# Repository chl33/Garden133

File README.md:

# Garden133 (v1.1.0)

Garden133 is a solar and battery-powered device for monitoring garden soil moisture levels.
It reads the moisture level of soil using a capacitive moisture sensor and transmits data via LoRa.

Please see the [Introducing Garden133](https://selectiveappeal.org/posts/garden133/) blog
post for a project overview.

## Features
- **Modern Web Interface:** A responsive Svelte-based UI for real-time status monitoring and calibration (accessible in Debug Mode).
- **Soil Moisture Sensing:** Capacitive sensor measurement with high-precision calibration and low-voltage filtering protection.
- **Dedicated Calibration Page:** View live ADC counts to precisely tune dry/wet thresholds.
- **Device Environmental Monitoring:** SHTC3 sensor for air temperature and humidity inside the device enclosure.
- **Power Management:** Solar charging, battery/5V rail monitoring, TP4056 charge/standby status reporting (Board v6+), and P-MOSFET moisture sensor power gating during deep sleep (Board v7+).
- **LoRa Communication:** Supports both HopeRF RFM95W (`SX1276`, Board v5–v7) and Ai-Thinker Ra-01SH (`SX1262`, Board v8+) modules to connect to a base station ([LoRa133](https://github.com/chl33/LoRa133)) for Home Assistant integration.
- **OTA Updates:** Support for wireless firmware updates.

## Hardware
This project includes the custom hardware design and 3D printable parts.

- **PCB Design:** KiCAD files are available in [`KiCAD/Garden133/`](KiCAD/Garden133/).
  - **Board v6.x:** Adds TP4056 charge/standby status inputs.
  - **Board v7.0:** Adds P-channel MOSFET (`AO3401A` on GPIO25) to power off the capacitive moisture sensor during sleep.
  - **Board v8.0:** Transitions to the Ai-Thinker Ra-01SH (`SX1262`) LoRa transceiver and an active-low debug DIP switch with external pull-up.
  
- **Enclosure & Fixtures:** OpenSCAD files for the waterproof enclosure, desiccant inserts, mounts, and solder-paste stencil fixtures are in [`OpenSCAD/`](OpenSCAD/).

## Firmware Dependencies
This firmware uses the [PlatformIO](https://platformio.org/) build system and depends on the following libraries:
- [og3](https://github.com/chl33/og3): Base C++ library for ESP32/Arduino.
- [og3x-lora](https://github.com/chl33/og3x-lora): LoRa module support (`SX1276` and `SX1262` via RadioLib).
- [og3x-satellite](https://github.com/chl33/og3x-satellite): Satellite architecture support.
- [og3x-shtc3](https://github.com/chl33/og3x-shtc3): SHTC3 temperature and humidity sensor support.

## Getting Started

### Prerequisites
- [PlatformIO Core](https://docs.platformio.org/en/latest/core/index.html) or VSCode with PlatformIO extension.
- Node.js (v22+) and `npm` (for building the embedded Svelte web UI).
- An ESP32-based Garden133 board.

### Configuration
The project uses `secrets.ini` and `local.ini` for local configuration and board definitions (both excluded from git):

1. **Setup Secrets & Local Board Environments:**
   Copy the example configuration files:
   ```bash
   cp secrets.ini.example secrets.ini
   cp local.ini.example local.ini
   ```
   - Edit `secrets.ini` to set `otaPassword` for Over-The-Air updates.
   - Edit `local.ini` to configure your board's `HARDWARE_VERSION_MAJOR` / `HARDWARE_VERSION_MINOR` (e.g., `6.2`, `7.0`, or `8.0`), upload port/IP, and optional UDP debug logging.

### Building & Flashing

1. **Build the firmware:**
   ```bash
   pio run
   ```

2. **Upload the firmware:**
   ```bash
   pio run --target upload
   ```

3. **Upload Filesystem (LittleFS):**
   This uploads the `data/` directory containing web resources.
   ```bash
   pio run --target uploadfs
   ```

## License
This project is licensed under the MIT License. See `LICENSE` for details.

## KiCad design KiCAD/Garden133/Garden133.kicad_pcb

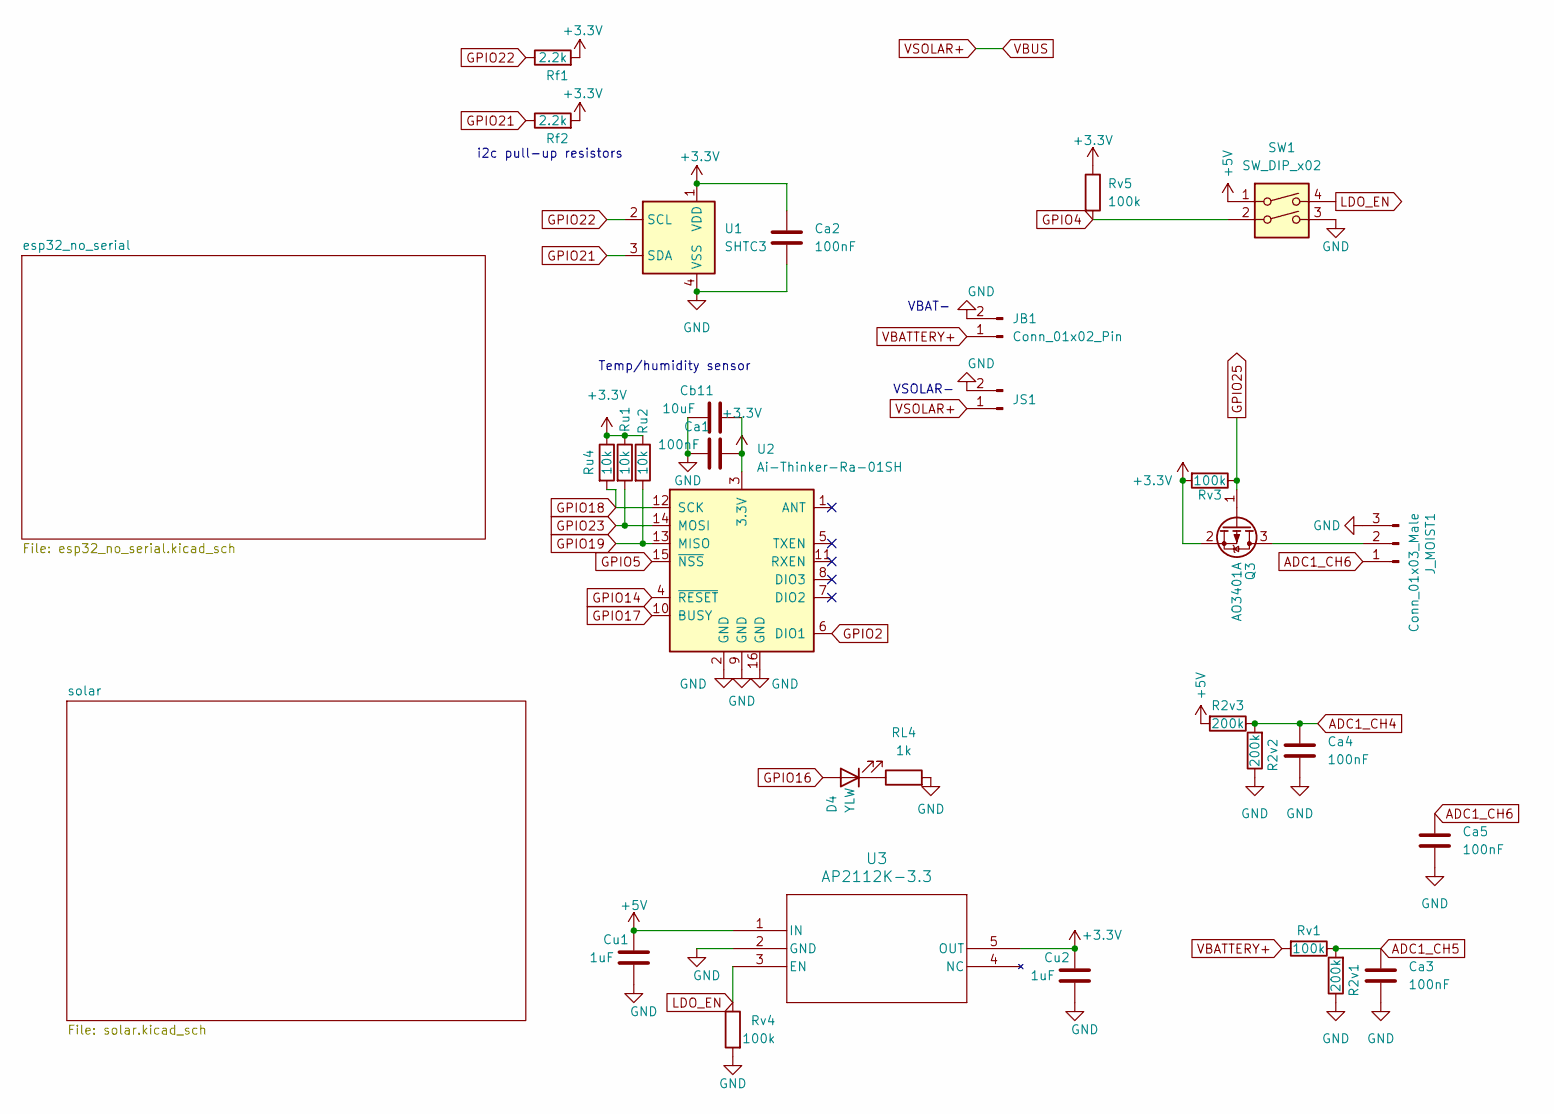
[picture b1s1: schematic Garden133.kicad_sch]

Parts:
Ca1, Ca2: 100nF; C_0603_1608Metric
Ca3, Ca4, Ca5: 100nF; C_0603_1608Metric_Pad1.08x0.95mm_HandSolder
Cb11: 10uF; C_0805_2012Metric_Pad1.18x1.45mm_HandSolder
Cu1, Cu2: 1uF; C_0805_2012Metric_Pad1.18x1.45mm_HandSolder
D4: YLW; LED_0603_1608Metric_Pad1.05x0.95mm_HandSolder
JB1: Conn_01x02_Pin; MOLEX_530470210
JS1: Conn_01x02_Pin; JST_XH_B2B-XH-A_1x02_P2.50mm_Vertical
J_MOIST1: Conn_01x03_Male; JST_XH_B3B-XH-A_1x03_P2.50mm_Vertical
Q3: AO3401A; SOT-23
R2v1, R2v2, R2v3: 200k; R_0603_1608Metric
RL4: 1k; R_0603_1608Metric_Pad0.98x0.95mm_HandSolder
Rf1, Rf2: 2.2k; R_0603_1608Metric
Ru1, Ru2, Ru4: 10k; R_0603_1608Metric
Rv1, Rv3, Rv4, Rv5: 100k; R_0603_1608Metric
SW1: SW_DIP_x02; SW_DIP_SPSTx02_Slide_6.7x6.64mm_W6.73mm_P2.54mm_LowProfile_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
U1: SHTC3; Sensirion_DFN-4-1EP_2x2mm_P1mm_EP0.7x1.6mm
U2: Ai-Thinker-Ra-01SH; Ai-Thinker-Ra-01-LoRa
U3: AP2112K-3.3; SOT-23-5

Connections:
+3.3V: Ca1.2, Ca2.1, Cb11.2, Cu2.1, Q3.2 (S), Rf1.2, Rf2.2, Ru1.1, Ru2.1, Ru4.1, Rv3.2, Rv5.1, U1.1 (VDD), U2.3 (3.3V), U3.5 (OUT); also elsewhere on the board
+5V: Cu1.1, R2v3.2, SW1.1, U3.1 (IN); also elsewhere on the board
ADC1_CH4: Ca4.2, R2v2.2, R2v3.1; also elsewhere on the board
ADC1_CH5: Ca3.2, R2v1.2, Rv1.1; also elsewhere on the board
ADC1_CH6: Ca5.2, J_MOIST1.1; also elsewhere on the board
GND: Ca1.1, Ca2.2, Ca3.1, Ca4.1, Ca5.1, Cb11.1, Cu1.2, Cu2.2, JB1.2, JS1.2, J_MOIST1.3, R2v1.1, R2v2.1, RL4.2, Rv4.2, SW1.3, U1.4 (VSS), U2.2 (GND), U2.9 (GND), U2.16 (GND), U3.2 (GND); also elsewhere on the board
GPIO2: U2.6 (DIO1); also elsewhere on the board
GPIO4: Rv5.2, SW1.2; also elsewhere on the board
GPIO5: U2.15 (~NSS); also elsewhere on the board
GPIO14: U2.4 (~RESET); also elsewhere on the board
GPIO16: D4.2 (A); also elsewhere on the board
GPIO17: U2.10 (BUSY); also elsewhere on the board
GPIO18: Ru4.2, U2.12 (SCK); also elsewhere on the board
GPIO19: Ru2.2, U2.13 (MISO); also elsewhere on the board
GPIO21: Rf2.1, U1.3 (SDA); also elsewhere on the board
GPIO22: Rf1.1, U1.2 (SCL); also elsewhere on the board
GPIO23: Ru1.2, U2.14 (MOSI); also elsewhere on the board
GPIO25: Q3.1 (G), Rv3.1; also elsewhere on the board
LDO_EN: Rv4.1, SW1.4, U3.3 (EN)
unnamed: D4.1 (K), RL4.1
unnamed: J_MOIST1.2, Q3.3 (D)
VBATTERY+: JB1.1, Rv1.2; also elsewhere on the board
VBUS: JS1.1; also elsewhere on the board

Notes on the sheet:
VSOLAR-
Temp/humidity sensor
i2c pull-up resistors
VBAT-

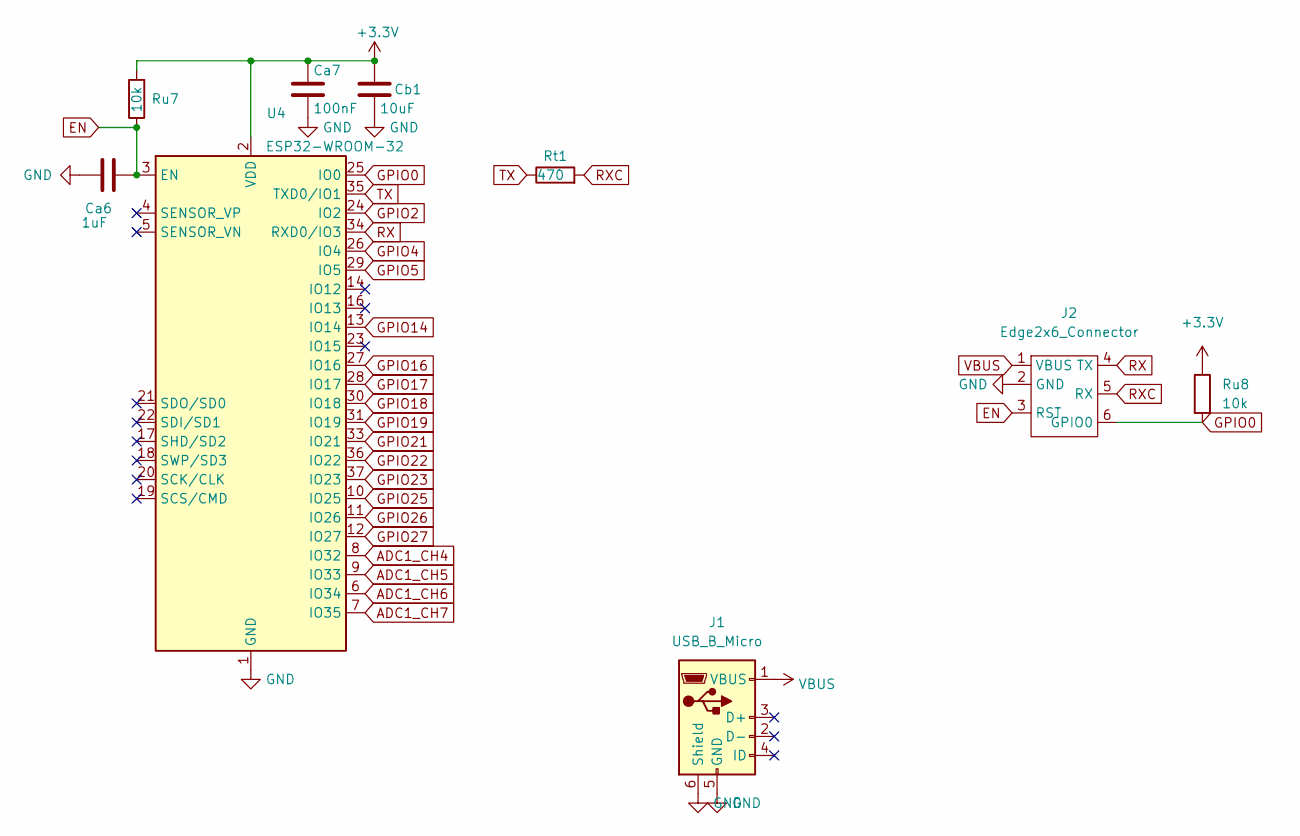
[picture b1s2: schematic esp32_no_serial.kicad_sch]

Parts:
Ca6: 1uF; C_0603_1608Metric
Ca7: 100nF; C_0603_1608Metric
Cb1: 10uF; C_0805_2012Metric_Pad1.18x1.45mm_HandSolder
J1: USB_B_Micro; USB_Micro-B_Amphenol_10118194_Horizontal
J2: Edge2x6_Connector; EdgeConnector_2x3
Rt1: 470; R_0603_1608Metric
Ru7: 10k; R_0603_1608Metric
Ru8: 10k; R_0603_1608Metric_Pad0.98x0.95mm_HandSolder
U4: ESP32-WROOM-32

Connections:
+3.3V: Ca7.1, Cb1.1, Ru7.2, Ru8.1, U4.2 (VDD); also elsewhere on the board
ADC1_CH4: U4.8 (IO32); also elsewhere on the board
ADC1_CH5: U4.9 (IO33); also elsewhere on the board
ADC1_CH6: U4.6 (IO34); also elsewhere on the board
ADC1_CH7: U4.7 (IO35); also elsewhere on the board
EN: Ca6.2, J2.3 (RST), Ru7.1, U4.3 (EN)
GND: Ca6.1, Ca7.2, Cb1.2, J1.5 (GND), J1.6 (Shield), J2.2 (GND), U4.1 (GND), U4.15 (GND), U4.38 (GND), U4.39 (GND); also elsewhere on the board
GPIO0: J2.6 (GPIO0), Ru8.2, U4.25 (IO0)
GPIO2: U4.24 (IO2); also elsewhere on the board
GPIO4: U4.26 (IO4); also elsewhere on the board
GPIO5: U4.29 (IO5); also elsewhere on the board
GPIO14: U4.13 (IO14); also elsewhere on the board
GPIO16: U4.27 (IO16); also elsewhere on the board
GPIO17: U4.28 (IO17); also elsewhere on the board
GPIO18: U4.30 (IO18); also elsewhere on the board
GPIO19: U4.31 (IO19); also elsewhere on the board
GPIO21: U4.33 (IO21); also elsewhere on the board
GPIO22: U4.36 (IO22); also elsewhere on the board
GPIO23: U4.37 (IO23); also elsewhere on the board
GPIO25: U4.10 (IO25); also elsewhere on the board
GPIO26: U4.11 (IO26); also elsewhere on the board
GPIO27: U4.12 (IO27); also elsewhere on the board
RX: J2.4 (TX), U4.34 (RXD0/IO3)
RXC: J2.5 (RX), Rt1.2
TX: Rt1.1, U4.35 (TXD0/IO1)
VBUS: J1.1 (VBUS), J2.1 (VBUS); also elsewhere on the board

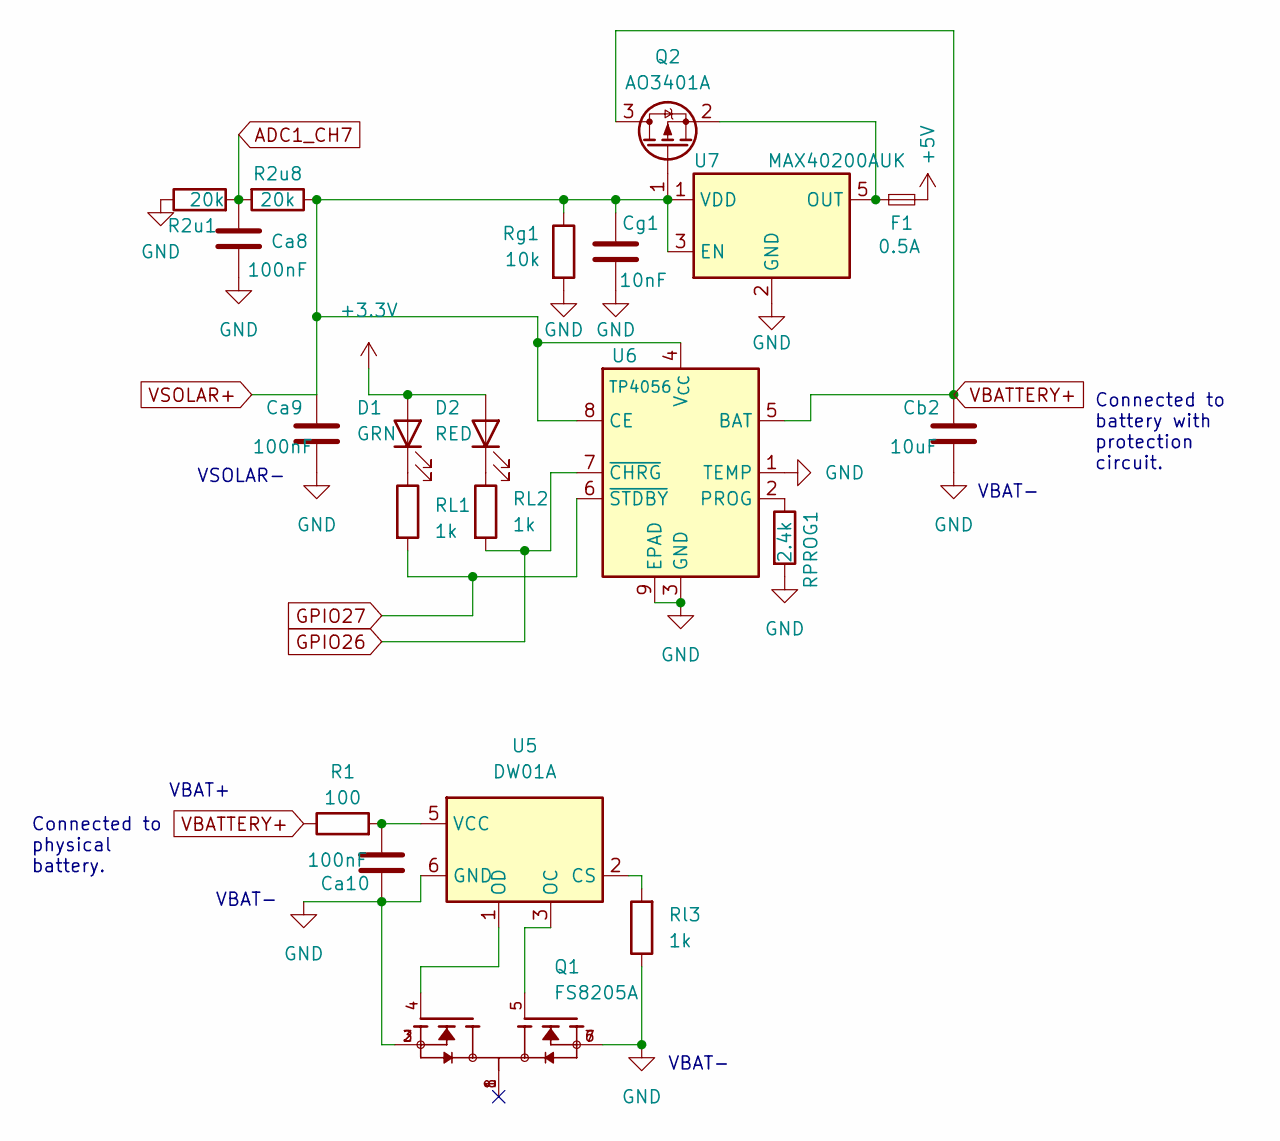
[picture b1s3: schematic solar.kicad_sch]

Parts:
Ca8, Ca9, Ca10: 100nF; C_0603_1608Metric_Pad1.08x0.95mm_HandSolder
Cb2: 10uF; C_0805_2012Metric_Pad1.18x1.45mm_HandSolder
Cg1: 10nF; C_0603_1608Metric_Pad1.08x0.95mm_HandSolder
D1: GRN; LED_0603_1608Metric_Pad1.05x0.95mm_HandSolder
D2: RED; LED_0603_1608Metric_Pad1.05x0.95mm_HandSolder
F1: 0.5A; D_0805_2012Metric
Q1: FS8205A; SOP65P640X120-8N; PARTREV 1.7
Q2: AO3401A; SOT-23
R1: 100; R_0603_1608Metric_Pad0.98x0.95mm_HandSolder
R2u1: 20k; R_0603_1608Metric_Pad0.98x0.95mm_HandSolder
R2u8: 20k; R_0603_1608Metric
RL1, RL2: 1k; R_0603_1608Metric_Pad0.98x0.95mm_HandSolder
RPROG1: 2.4k; R_0603_1608Metric_Pad0.98x0.95mm_HandSolder
Rg1: 10k; R_0603_1608Metric_Pad0.98x0.95mm_HandSolder
Rl3: 1k; R_0603_1608Metric_Pad0.98x0.95mm_HandSolder
U5: DW01A; SOT-23-6; LCSC C61503
U6: TP4056; SOIC-8-1EP_3.9x4.9mm_P1.27mm_EP2.41x3.3mm_ThermalVias
U7: MAX40200AUK; SOT-23-5

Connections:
+3.3V: D1.2 (A), D2.2 (A); also elsewhere on the board
+5V: F1.2; also elsewhere on the board
ADC1_CH7: Ca8.2, R2u1.2, R2u8.2; also elsewhere on the board
GND: Ca8.1, Ca9.2, Ca10.2, Cb2.2, Cg1.2, Q1.2, Q1.3, Q1.6, Q1.7, R2u1.1, RPROG1.2, Rg1.2, Rl3.1, U5.6 (GND), U6.1 (TEMP), U6.3 (GND), U6.9 (EPAD), U7.2 (GND); also elsewhere on the board
GPIO26: RL2.2, U6.7 (~CHRG); also elsewhere on the board
GPIO27: RL1.2, U6.6 (~STDBY); also elsewhere on the board
unnamed: D1.1 (K), RL1.1
unnamed: D2.1 (K), RL2.1
unnamed: F1.1, Q2.2 (S), U7.5 (OUT)
unnamed: Rl3.2, U5.2 (CS)
unnamed: Q1.5, U5.3 (OC)
unnamed: Q1.4, U5.1 (OD)
unnamed: Ca10.1, R1.2, U5.5 (VCC)
unnamed: RPROG1.1, U6.2 (PROG)
VBATTERY+: Cb2.1, Q2.3 (D), R1.1, U6.5 (BAT); also elsewhere on the board
VBUS: Ca9.1, Cg1.1, Q2.1 (G), R2u8.1, Rg1.1, U6.4 (V_{CC}), U6.8 (CE), U7.1 (VDD), U7.3 (EN); also elsewhere on the board

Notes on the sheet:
VBAT-
Connected to battery with protection circuit.
VBAT+
Connected to physical battery.
VSOLAR-

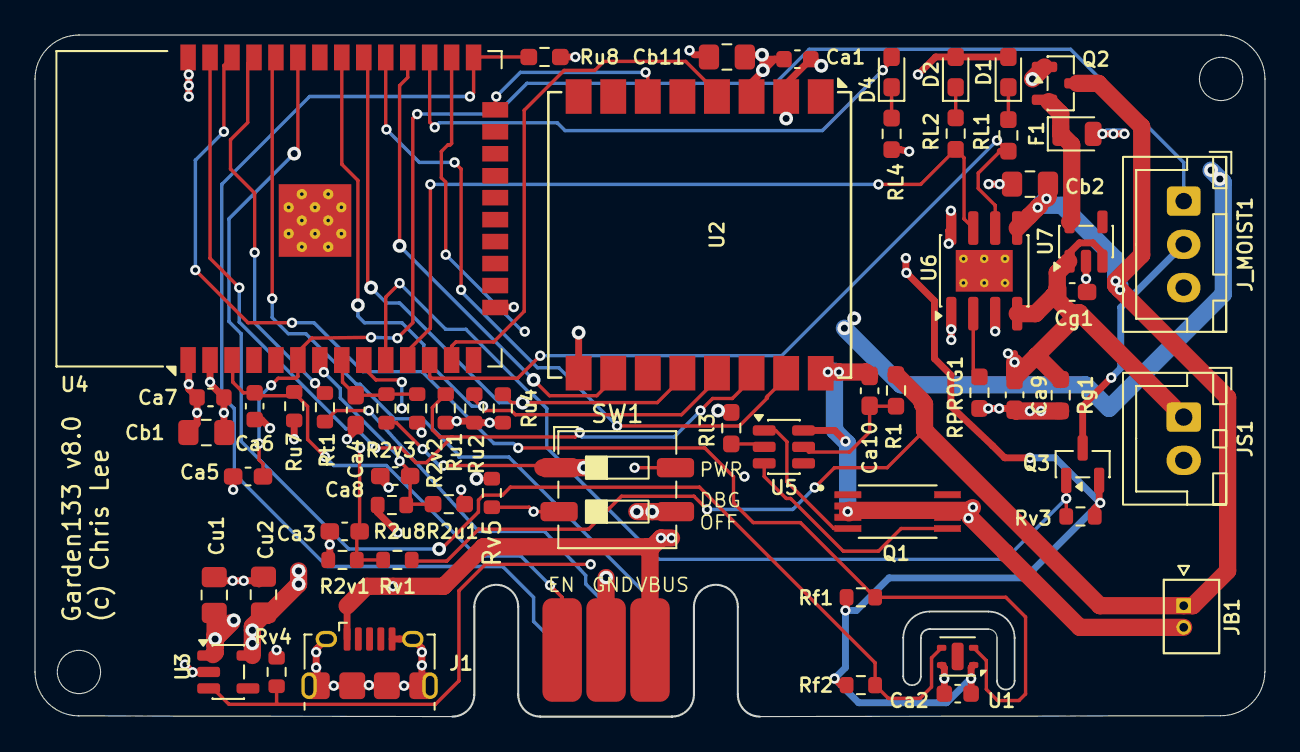
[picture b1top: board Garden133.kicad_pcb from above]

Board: 4 copper layers, 71.0 x 39.4 mm, 60 parts (0 on the bottom side), 39 nets.

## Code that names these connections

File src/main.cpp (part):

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constexpr int kLoraDio0 = 2;
#endif

constexpr int kFiveVPin = 32;      // ADC1_CH4
constexpr int kBatteryPin = 33;    // ADC1_CH5
constexpr int kMoisturePin = 34;   // ADC1_CH6
constexpr int kSolarPlusPin = 35;  // ADC1_CH7
#ifdef HAVE_MOISTURE_POWER_CTL
// Gate control for AO3401A P-FET moisture sensor power switch
constexpr int kMoisturePowerPin = 25;
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constexpr int kDebugSwitchPin = 04;
inline bool read_debug_switch() {
#if HARDWARE_VERSION_MAJOR >= 8
  // Board v8+: Switch 2 connects GPIO4 to GND with external pull-up Rv5.
  // Switch ON (closed) = GND (LOW) -> Debug Mode.
  return digitalRead(kDebugSwitchPin) == LOW;
#else
  // Board < v8: Push switch connects GPIO4 to 3.3V when activated.
  // HIGH -> Debug Mode.
  return digitalRead(kDebugSwitchPin) == HIGH;
#endif
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
  while (true) {
    // --- Test 1: BUSY pin pull-up / pull-down float check ---
    Serial.println("\n--- [Test 1] BUSY Pin (Pin 10 / GPIO17) Connection Check ---");
    pinMode(17, INPUT_PULLUP);
    delay(2);
    int busy_pu = digitalRead(17);
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
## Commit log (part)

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2025-06-15 initial version
2025-06-15 code moved to og3
2025-06-15 Update for board v6
    - Added OpenSCAD models for Solar panel mount, tray for board+battery
    - ADC Adjustment because using 220k resistors, not 200k.
    - Licenses updated
    - Remove support for v4 boards, update ADC slopes
    - Board v6.0 (ordered)
    - Support publishing more data via LoRa.
2025-06-15 Soil-sensor potting case update
2025-06-15 Read temp/humidity and moisture sensors, and send via LoRa+MQTT
2025-06-15 solar ADC divide-down is now 2
2025-06-15 ADC counts change from number -> unspecified
2025-06-15 Soil moisture sensor potting frame -- initial version
2025-06-15 WIP -- KiCAD, packet format, device protos
2025-06-15 Send full device info every hour, brief info otherwise.
2025-06-15 Update PCB
    - Button controls power to 3.3V LDO
    - DIO readings for STDBY and CHRG
2025-06-15 Board version 5
2025-06-15 Updated device protobuf, got LoRa working.
2025-06-15 Allow turning-off debug mode.
    Note that this does not power-down WiFi.
2025-06-15 support blinking the LED
2025-06-15 Soil moisture sensor potting frame -- version 2
2025-06-15 First draft of new moisture sensor cap
2025-06-15 og3->0.3.16, use crc32 for LoRa packets, ignore moisture when <3.3V
2025-06-15 Solar panel holder for smaller panel
2025-06-15 Register moisture reading as "measurement" state-class for HA stats
2025-06-15 Attempt to avoid brown-out during desc-send
    Adjustments to deal with the fact that boards seemed to be browning-out when
    descriptions packets were being sent every second. Maybe the LDO+capacitors
    cannot keep up with this level of power usage?
    - Slow desc-sends to 1 every 5 seconds.
    - Make sure serial logging is turned off after USB code update.
    Maybe the board needs a bulk capacitor for 3.3V?
2025-06-15 Update: version -> 0.4.0
    - Fix boot-count, seq_id
    - Had initializers for some rtc values such as boot count, so these were being
    reset after sleep.
    - Fix logic for sending sensor-reading descriptions every hour.
    - Board stays alive a short time after sending messages to blink led.
2025-06-15 Better use of constants
2025-06-15 Garden133 Board v6.2 (ordered from PCBWay)
2025-06-15 Fix sleep timing
2025-06-15 version tweaks
2025-06-15 Use updates to og3x-lora, new og3x-satellite repositories.
    - Allow LoRa to be configurable via web interface.
    - Check payload size for US FCC reg (400msec max dwell).
2025-06-15 Fix led-blinking
2025-06-15 boards update
2025-06-15 Version 4a of moisture sensor cap
    - Shorter
    - Thinner slot for sensor board.
    - Shrink hole for connector
2025-06-15 cleanup platform.ini
2025-06-15 Update how config determines text-logging method
2025-06-15 Version 2 of moisture sensor cap
    - More space for connector
    - Tighter hole for sensor
    - Clamp top & bottom around the wire.
2025-06-15 Version 4 of moisture sensor cap
    - Shorter
    - Thinner slot for sensor board.
    - Shrink hole for connector
2025-06-15 Cleanup loop()
2025-06-15 Fixes to avoid brown-outs
    - Only send one packet between sleeping after initial sensor descriptions are sent.
    - Each hour, for the first N-packets, send information about the N-th sensor.
    In the first packet send the device info.
    - The board reliably browns-out after sending 2 LoRa packets and never recovers, when
    battery-powered at least (and maybe also when connected to the moisture sensor).
    - Add more bits to the boot-count in rtc memory. It was going to roll over after 45
2025-06-15 Attempt to make sleep configurable, more consistent wakeup.
2025-06-15 OpenSCAD: waterproof enclosure, stls for soil moisture cap
2025-06-15 Version 3 of moisture sensor cap
    - Thicker minimum wall thickness.
    - More space at top of connector for wire into JST
    - Lip at side of box to lock it into place
    - Screw holes near top (away from point) of sensor)
2025-06-15 fix link
2025-06-19 Fix 20k resistor (was 10k)
2025-06-19 Board v6.2 update: standby/charge detection.
    Maybe also fix hourly update?
2025-06-19 Example secrets pio config
2025-06-19 update for board v6.2 (#1)
    - Fix 20k resistor
    - Board v6.2 update: standby/charge detection
    -Maybe also fix hourly update?
2025-06-22 KiCAD model: remove duplicate battery connection
2025-06-22 Fix for standby/charge DIn detection
2025-06-22 Updates (#2)
    * KiCAD model: remove duplicate battery connection
    * Fix for standby/charge DIn detection
2025-07-07 KiCAD v62 fixes, README update, code update (#3)
    * KiCAD model: remove duplicate battery connection
    * Code: Fix for standby/charge DIn detection
    * Update README
2025-07-19 version -> 0.6.0
    - Used updated og3x-satellite with updated protocol
    - Set board name as device name in device protobuf
    - Set model name as device_type (new field) in device protobuf
2025-07-19 version -> 0.6.0 (#4)
    - Used updated og3x-satellite with updated protocol
    - Set board name as device name in device protobuf
    - Set model name as device_type (new field) in device protobuf
2025-10-18 Update moisture cap -- needs testing
2025-10-18 shorten cap, add more space for connector
2025-10-18 Slightly more space for soil moisture sensor in y direction
2025-10-18 shorten screw-hole
2025-10-19 moisture cap STL file update
2025-10-19 dependency cleanups, code comments
2025-10-19 soil moisture cap update (#5)
    - Updated soil moisture cap design.
    - Depdencency cleanups to get the build to work again.
    - Code-comment edits
2026-01-28 board updates
2026-01-28 README updates
2026-01-28 platform.ini: update dependencies
2026-01-28 added uploadHostPort to secrets example
2026-01-28 Board update, README update (#6)
    - Board updae
    - README update, assisted by Gemini.
    - Bump dependencies.
2026-03-22 license-check update
2026-03-22 update to newer og3x-lora (gemini)
2026-03-22 Gemini updates to get the code to compile
2026-03-22 let /lora URL handle POSTs
2026-03-25 gemini fixes for new dependency system
2026-03-29 copyright headers
2026-03-29 Svelte interface (gemini)
2026-03-31 start of local board reconfiguration
2026-03-31 web interface fixes (gemini)
2026-03-31 Separate moisture sensor calibration page (gemini)
2026-04-01 reordered adc reading
2026-04-01 opened board in kicad
2026-04-02 platformio.ini: update deps to public versions
2026-04-02 Updates for version 1.0.0
2026-04-03 Add local.ini.example, use in github action CI build
2026-04-03 Add web interface to README
2026-04-03 update build workflow for Svelta build
2026-04-03 Version 1.0.0 (#7)
    ## [1.0.0] - 2026-03-29
    ### Added
    - New responsive Svelte web interface for status monitoring and configuration (Debug Mode).
    - JSON API for full device control and status reporting.
    - Standardized `camelCase` naming for all API keys and internal variables.
    - Dedicated Moisture Calibration page with live ADC count monitoring.
2026-04-03 Bump actions/setup-python from 5 to 6
    Bumps [actions/setup-python](https://github.com/actions/setup-python) from 5 to 6.
    - [Release notes](https://github.com/actions/setup-python/releases)
    - [Commits](https://github.com/actions/setup-python/compare/v5...v6)
    ---
    updated-dependencies:
    - dependency-name: actions/setup-python
2026-04-03 Bump actions/setup-node from 4 to 6
    Bumps [actions/setup-node](https://github.com/actions/setup-node) from 4 to 6.
    - [Release notes](https://github.com/actions/setup-node/releases)
    - [Commits](https://github.com/actions/setup-node/compare/v4...v6)
    ---
    updated-dependencies:
    - dependency-name: actions/setup-node
2026-04-03 Bump actions/cache from 4 to 5
    Bumps [actions/cache](https://github.com/actions/cache) from 4 to 5.
    - [Release notes](https://github.com/actions/cache/releases)
    - [Changelog](https://github.com/actions/cache/blob/main/RELEASES.md)
    - [Commits](https://github.com/actions/cache/compare/v4...v5)
    ---
    updated-dependencies:
2026-04-03 Bump actions/checkout from 4 to 6
    Bumps [actions/checkout](https://github.com/actions/checkout) from 4 to 6.
    - [Release notes](https://github.com/actions/checkout/releases)
    - [Changelog](https://github.com/actions/checkout/blob/main/CHANGELOG.md)
    - [Commits](https://github.com/actions/checkout/compare/v4...v6)
    ---
    updated-dependencies:
2026-06-18 Bump actions/checkout from 4 to 7
    Bumps [actions/checkout](https://github.com/actions/checkout) from 4 to 7.
    - [Release notes](https://github.com/actions/checkout/releases)
    - [Changelog](https://github.com/actions/checkout/blob/main/CHANGELOG.md)
    - [Commits](https://github.com/actions/checkout/compare/v4...v7)
    ---
    updated-dependencies:
2026-06-23 Bump actions/cache from 4 to 6
    Bumps [actions/cache](https://github.com/actions/cache) from 4 to 6.
    - [Release notes](https://github.com/actions/cache/releases)
    - [Changelog](https://github.com/actions/cache/blob/main/RELEASES.md)
    - [Commits](https://github.com/actions/cache/compare/v4...v6)
    ---
    updated-dependencies:

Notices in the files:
src/main.cpp:
Copyright (c) 2026 Chris Lee and contributors.
Licensed under the MIT license. See LICENSE file in the project root for details.
